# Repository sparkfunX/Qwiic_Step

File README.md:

SparkX Qwiic Step
========================================

[*SparkX Qwiic Step (SPX-15951)*](https://www.sparkfun.com/products/15951)

Qwiic Step features the A4988 stepper motor driver IC. Send commands using the I2C bus to configure your stepper motor movements. Easily attach and set up a limit switch or E-Stop and use our new favorite latching terminals to solderlessly and screwlessly attach motor and power.

Repository Contents
-------------------

* **/Documentation** - Data sheets, additional product information
* **/Firmware** - Firmware used on Qwiic Step
* **/Hardware** - Eagle design files (.brd, .sch)
* **/Production** - Production panel files (.brd)

Documentation
--------------
* **[SparkFun Qwiic Step Arduino Library](https://github.com/sparkfun/SparkFun_Qwiic_Step_Arduino_Library)** - Arduino library for the SparkX Qwiic Step.
* **[SparkFun Fritzing repo](https://github.com/sparkfun/Fritzing_Parts)** - Fritzing diagrams for SparkFun products.
* **[SparkFun 3D Model repo](https://github.com/sparkfun/3D_Models)** - 3D models of SparkFun products. 
* **[SparkFun Graphical Datasheets](https://github.com/sparkfun/Graphical_Datasheets)** -Graphical Datasheets for various SparkFun products.

License Information
-------------------

This product is _**open source**_! 

Please review the LICENSE.md file for license information. 

If you have any questions or concerns on licensing, please contact technical support on our [SparkFun forums](https://forum.sparkfun.com/viewforum.php?f=152).

Distributed as-is; no warranty is given.

- Your friends at SparkFun.

_<COLLABORATION CREDIT>_

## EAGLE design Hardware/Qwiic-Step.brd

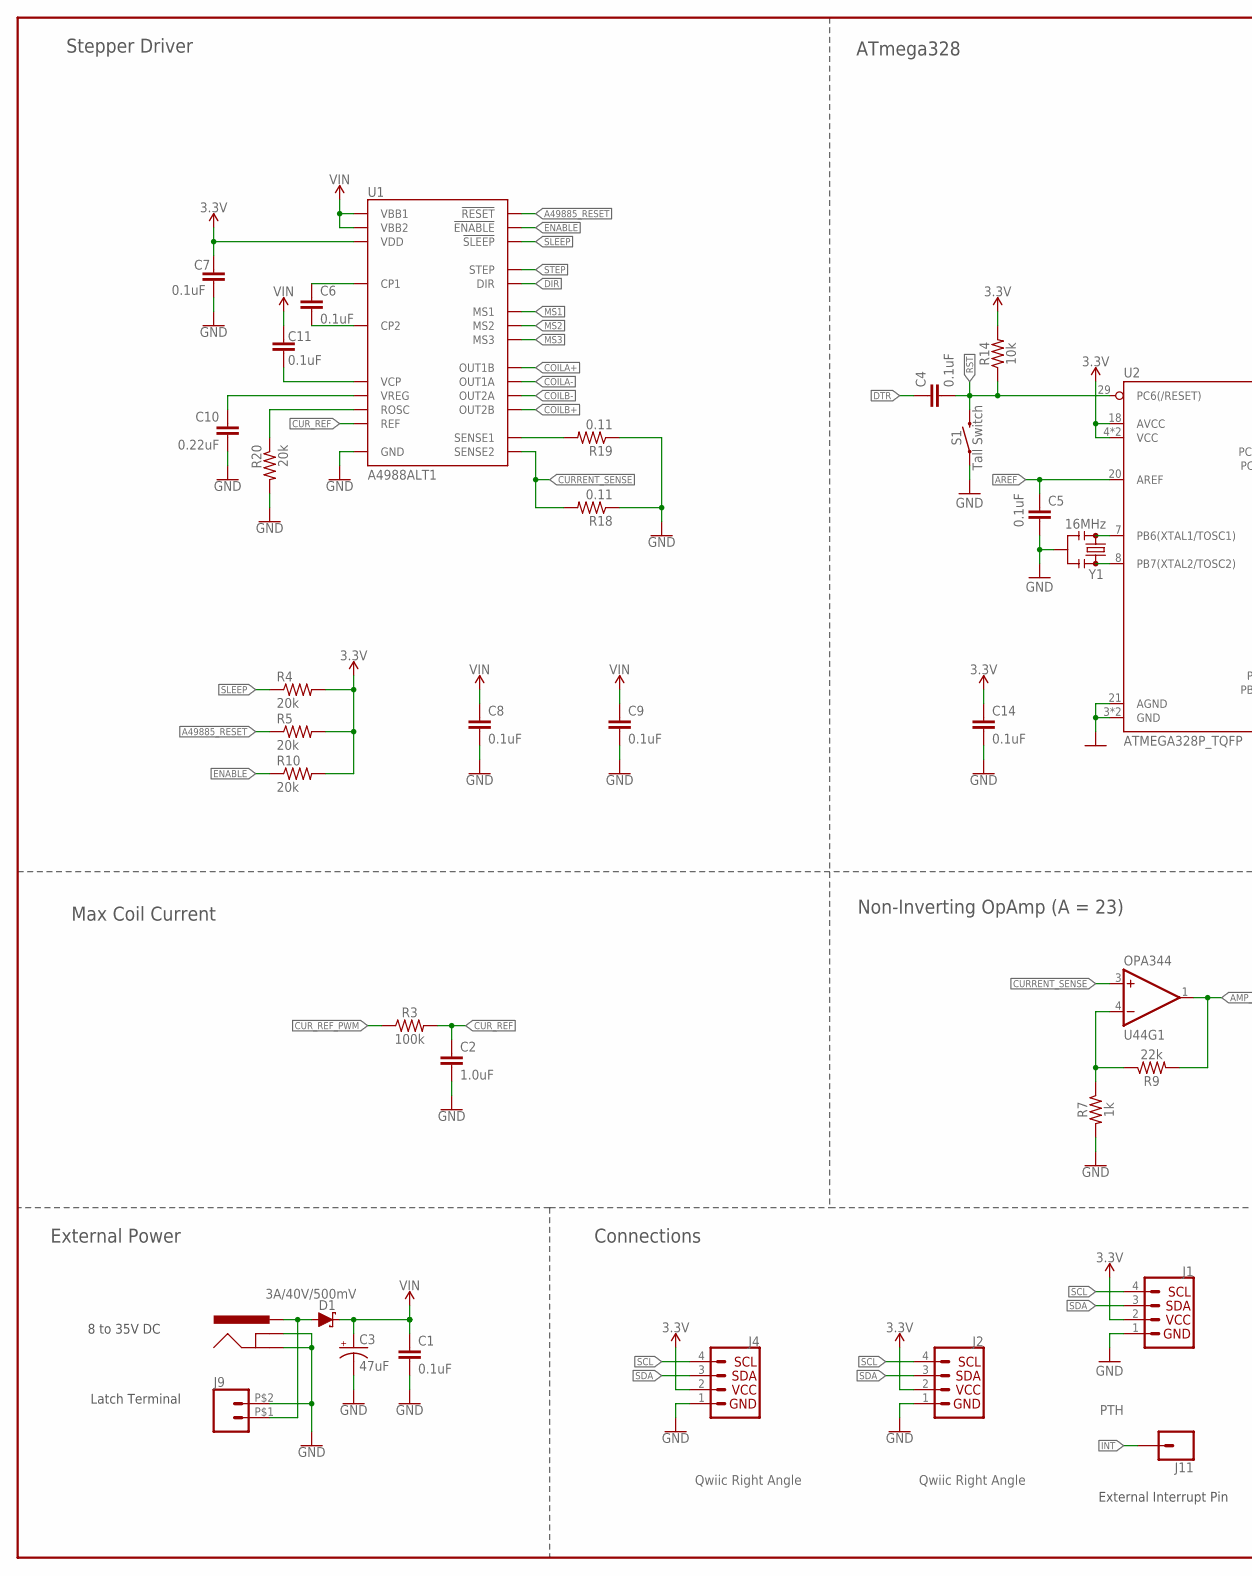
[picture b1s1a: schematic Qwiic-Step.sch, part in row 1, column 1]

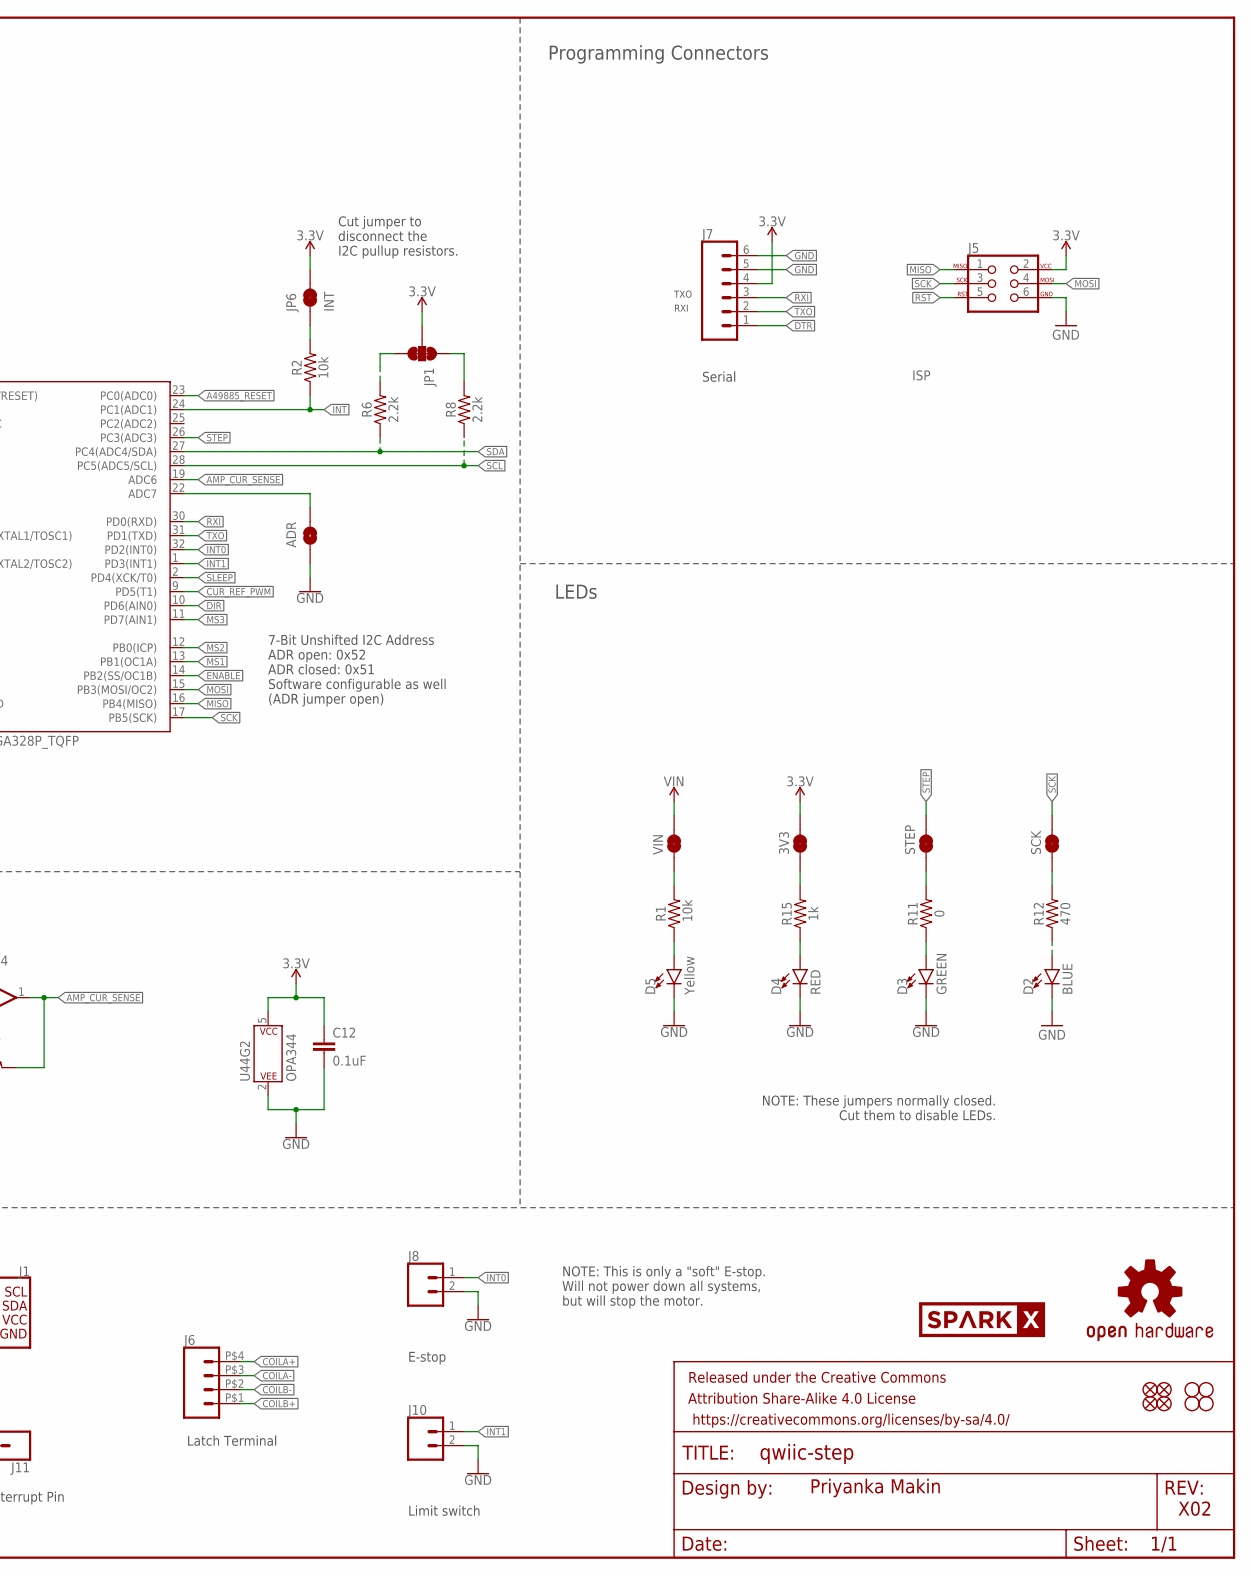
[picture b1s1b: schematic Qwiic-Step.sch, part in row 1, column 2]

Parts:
3V3: JUMPER-SMT_2_NC_TRACE_SILK; SMT-JUMPER_2_NC_TRACE_SILK
ADR: ADR; SMT-JUMPER_2_NO_SILK
C1, C4, C5, C6, C7, C8, C9, C11, C12, C14: 0.1uF; 0603
C2: 1.0uF; 0603
C3: 47uF; PANASONIC_D
C10: 0.22uF; 0603
D1: 3A/40V/500mV; SMA-DIODE
D2: BLUE; LED-0603
D3: GREEN; LED-0603
D4: RED; LED-0603
D5: Yellow; LED-0603
FD1, FD2, FD3, FD4: FIDUCIAL1X2; FIDUCIAL-1X2
FRAME2: FRAME-LEDGER; CREATIVE_COMMONS
J1: PTH; 1X04_NO_SILK
J2, J4: Qwiic Right Angle; JST04_1MM_RA
J3: 5.5x2.1mm Barrel; POWER_JACK_SMD
J5: ISP; 2X3_TEST_POINTS
J6: CONN_04LATCH; LATCHTERMINAL-5MM-4
J7: CONN_06NO_SILK_NO_POP; 1X06_NO_SILK
J8, J10: CONN_02-JST-2MM-SMT; JST-2-SMD
J9: CONN_02LATCH_2; LATCHTERMINAL-5MM-2
J11: CONN_01PTH_NO_SILK_YES_STOP; 1X01_NO_SILK
JP1: JUMPER-SMT_3_2-NC_TRACE_SILK; SMT-JUMPER_3_2-NC_TRACE_SILK
JP6: INT; SMT-JUMPER_2_NC_TRACE_SILK
JP7, JP8, JP9, JP10: STAND-OFF
LOGO1: OSHW-LOGOMINI; OSHW-LOGO-MINI
R1, R2, R14: 10k; 0603
R3: 100k; 0603
R4, R5, R10, R20: 20k; 0603
R6, R8: 2.2k; 0603
R7, R15: 1k; 0603
R9: 22k; 0603
R11: 0; 0603
R12: 470; 0603
R18, R19: 0.11; 2010
S1: Tall Switch; TACTILE_SWITCH_SMD_5.2MM
SCK: JUMPER-SMT_2_NC_TRACE_SILK; SMT-JUMPER_2_NC_TRACE_SILK
STEP: JUMPER-SMT_2_NC_TRACE_SILK; SMT-JUMPER_2_NC_TRACE_SILK
U1: A4988ALT1; QFN-28-5MM
U2: ATMEGA328P_TQFP; TQFP32-08
U44: OPA344; SOT23-5
U$49: SPARKX-LOGO4; SPARKX-MEDIUM
VIN: JUMPER-SMT_2_NC_TRACE_SILK; SMT-JUMPER_2_NC_TRACE_SILK
Y1: 16MHz; RESONATOR-SMD-3.2X1.3

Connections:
3.3V: 3V3.2, C7.1, C12.1, C14.1, J1.2 (VCC), J2.2, J4.2, J5.2, J7.4, JP1.2, JP6.2, R4.2, R5.2, R10.2, R14.2, U1.15 (VDD), U2.4 (VCC), U2.6 (VCC), U2.18 (AVCC), U44.5 (P$V+)
!ENABLE!: R10.1, U1.2 (!ENABLE!), U2.14 (PB2(SS/OC1B))
!RST!: C4.2, J5.5, R14.1, S1.3 (2), S1.4 (2), U2.29 (PC6(/RESET))
!SLEEP!: R4.1, U1.14 (!SLEEP!), U2.2 (PD4(XCK/T0))
A49885_!RESET!: R5.1, U1.12 (!RESET!), U2.23 (PC0(ADC0))
AMP_CUR_SENSE: R9.2, U2.19 (ADC6), U44.1 (OUT)
AREF: C5.1, U2.20 (AREF)
COILA+: J6.P$4 (4), U1.21 (OUT1B)
COILA-: J6.P$3 (3), U1.24 (OUT1A)
COILB+: J6.P$1 (1), U1.1 (OUT2B)
COILB-: J6.P$2 (2), U1.26 (OUT2A)
CURRENT_SENSE: R18.2, U1.27 (SENSE2), U44.3 (+IN)
CUR_REF: C2.1, R3.2, U1.17 (REF)
CUR_REF_PWM: R3.1, U2.9 (PD5(T1))
DIR: U1.19 (DIR), U2.10 (PD6(AIN0))
DTR: C4.1, J7.1
GND: ADR.2, C1.2, C2.2, C3.-, C5.2, C7.2, C8.2, C9.2, C10.2, C12.2, C14.2, D2.C, D3.C, D4.C, D5.C, J1.1 (GND), J2.1, J3.GND (GNDBREAK), J3.P$4 (GND), J4.1, J5.6, J7.5, J7.6, J8.2 (1), J9.P$2 (2), J10.2 (1), R7.2, R18.1, R19.1, R20.2, S1.1, S1.2 (1), U1.3 (GND), U1.18 (GND), U1.29 (GND), U2.3 (GND), U2.5 (GND), U2.21 (AGND), U44.2 (P$V-), Y1.2
INT: J11.1, R2.1, U2.24 (PC1(ADC1))
INT0: J8.1 (2), U2.32 (PD2(INT0))
INT1: J10.1 (2), U2.1 (PD3(INT1))
MISO: J5.1, U2.16 (PB4(MISO))
MOSI: J5.4, U2.15 (PB3(MOSI/OC2))
MS1: U1.9 (MS1), U2.13 (PB1(OC1A))
MS2: U1.10 (MS2), U2.12 (PB0(ICP))
MS3: U1.11 (MS3), U2.11 (PD7(AIN1))
unnamed: D3.A, R11.1
unnamed: R7.1, R9.1, U44.4 (-IN)
unnamed: R19.2, U1.23 (SENSE1)
unnamed: R1.2, VIN.1
unnamed: JP6.1, R2.2
unnamed: ADR.1, U2.22 (ADC7)
unnamed: D1.A, J3.VIN0 (PWR), J9.P$1 (1)
unnamed: C6.1, U1.4 (CP1)
unnamed: C6.2, U1.5 (CP2)
unnamed: D5.A, R1.1
unnamed: R11.2, STEP.1
unnamed: D2.A, R12.1
unnamed: U2.7 (PB6(XTAL1/TOSC1)), Y1.1
unnamed: U2.8 (PB7(XTAL2/TOSC2)), Y1.3
unnamed: JP1.3, R6.2
unnamed: JP1.1, R8.2
unnamed: R12.2, SCK.1
unnamed: R20.1, U1.13 (ROSC)
unnamed: C10.1, U1.8 (VREG)
unnamed: C11.1, U1.6 (VCP)
unnamed: D4.A, R15.1
unnamed: 3V3.1, R15.2
RXI: J7.3, U2.30 (PD0(RXD))
SCK: J5.3, SCK.2, U2.17 (PB5(SCK))
SCL: J1.4 (SCL), J2.4, J4.4, R8.1, U2.28 (PC5(ADC5/SCL))
SDA: J1.3 (SDA), J2.3, J4.3, R6.1, U2.27 (PC4(ADC4/SDA))
STEP: STEP.2, U1.16 (STEP), U2.26 (PC3(ADC3))
TXO: J7.2, U2.31 (PD1(TXD))
VIN: C1.1, C3.+, C8.1, C9.1, C11.2, D1.C, U1.22 (VBB1), U1.28 (VBB2), VIN.2

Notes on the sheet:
8 to 35V DC
Stepper Driver
Connections
Max Coil Current
External Power
ATmega328
TXO
RXI
Limit switch
E-stop
External Interrupt Pin
Latch Terminal
Priyanka Makin
X02
LEDs
Programming Connectors
Non-Inverting OpAmp (A = 23)
Serial
NOTE: These jumpers normally closed. Cut them to disable LEDs.
NOTE: This is only a "soft" E-stop. Will not power down all systems, but will stop the motor.
7-Bit Unshifted I2C Address ADR open: 0x52 ADR closed: 0x51 Software configurable as well (ADR jumper open)
Cut jumper to disconnect the I2C pullup resistors.

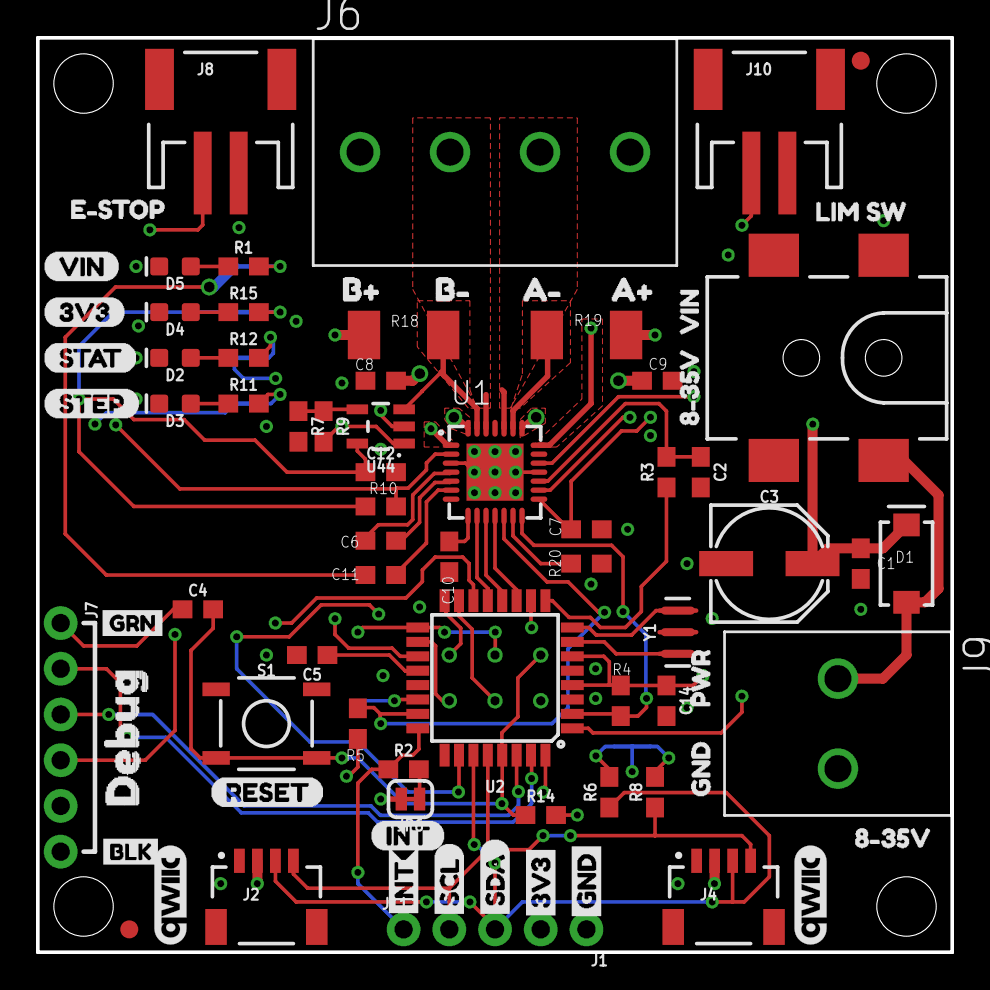
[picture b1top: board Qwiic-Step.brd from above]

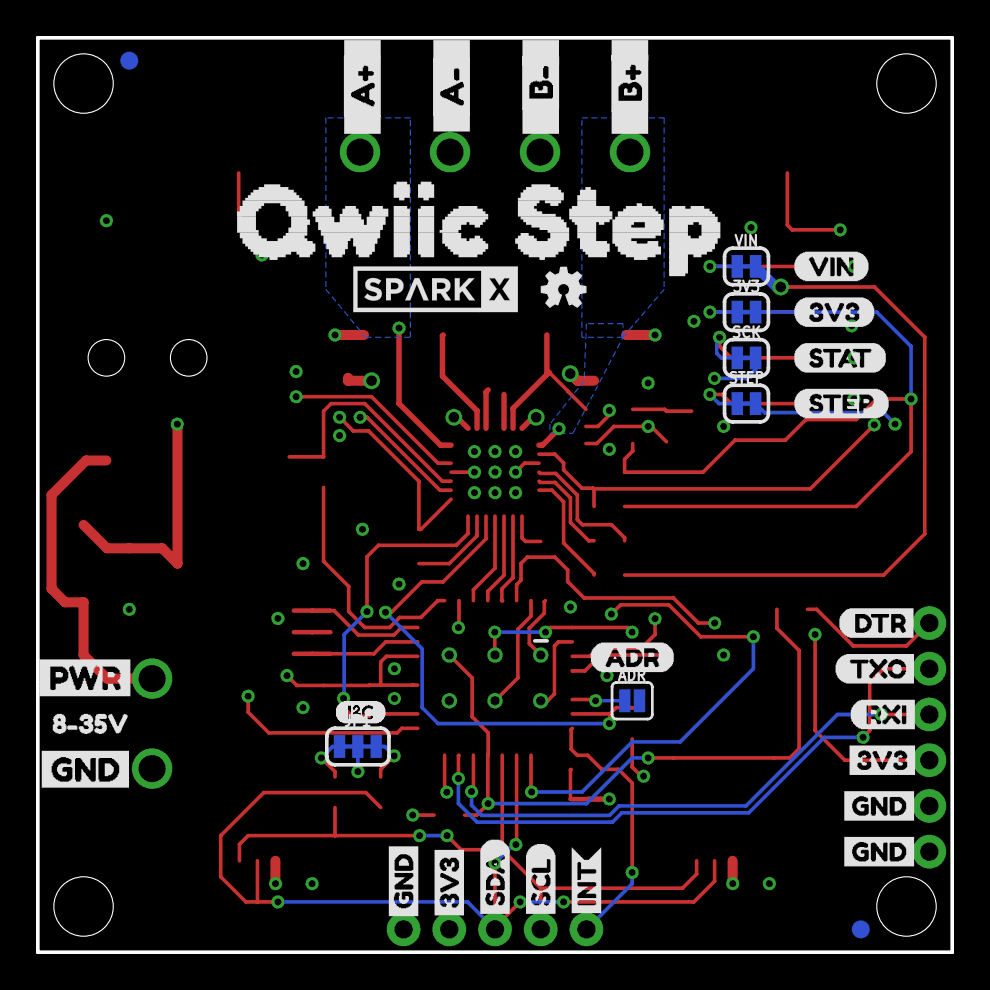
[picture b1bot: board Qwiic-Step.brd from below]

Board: 4 copper layers, 50.8 x 50.8 mm, 122 parts (37 on the bottom side), 54 nets.

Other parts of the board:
U$1: 3V30
U$2: 3V37
U$3: GND8
U$4: STAT5
U$5: SCL5
U$6: SDA6
U$7: STEP4
U$8: VIN3
U$9, U$29: QWIIC_5.5MM
U$10, U$11, U$40: 8#35V0
U$12: VIN1
U$13: STAT0
U$14: E#STOP2
U$15, U$16: I_SUPER2_C-()-03
U$17, U$45: 3V31
U$18: DTR4
U$19: DEBUG0
U$20: BLK2
U$21, U$22, U$44: GND0
U$23: LIM_SW3
U$24, U$30: INT4
U$25: ADR0
U$26: 3V35
U$27: RESET1
U$28: GRN1
U$31: GND6
U$32, U$54: A#2
U$33: SDA4
U$34: SCL3
U$35: RXI3
U$36, U$55: A#3
U$37: STEP2
U$38: VIN0
U$41: INT2
U$42: GND1
U$43: PWR0
U$46, U$57: B#4
U$47, U$58: B#5
U$48: TXO2
U$53: PWR1
U$56: QWIIC_STEP0

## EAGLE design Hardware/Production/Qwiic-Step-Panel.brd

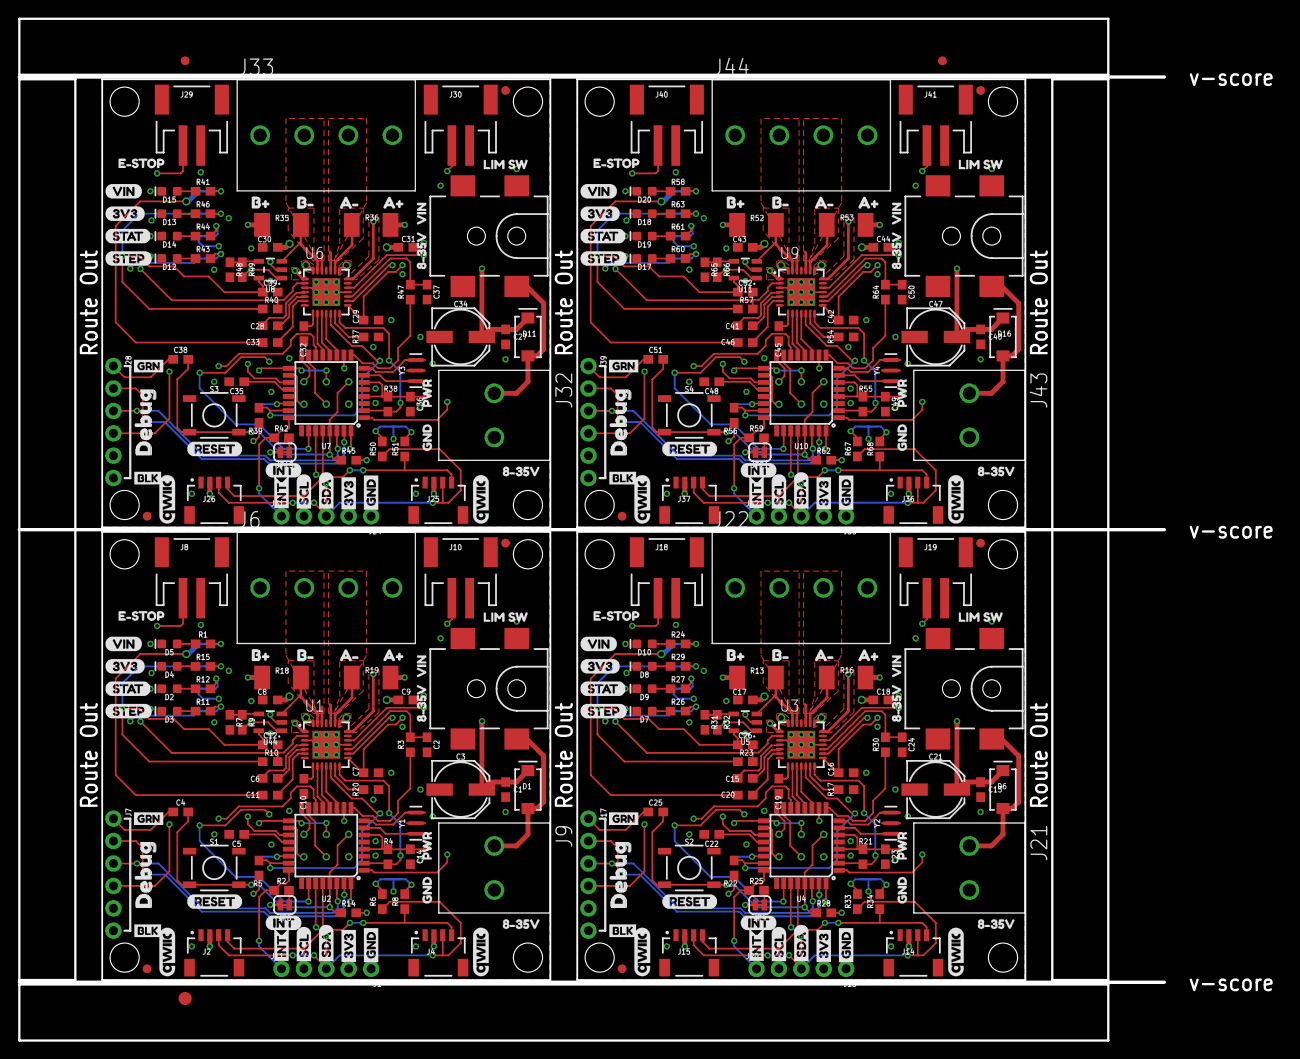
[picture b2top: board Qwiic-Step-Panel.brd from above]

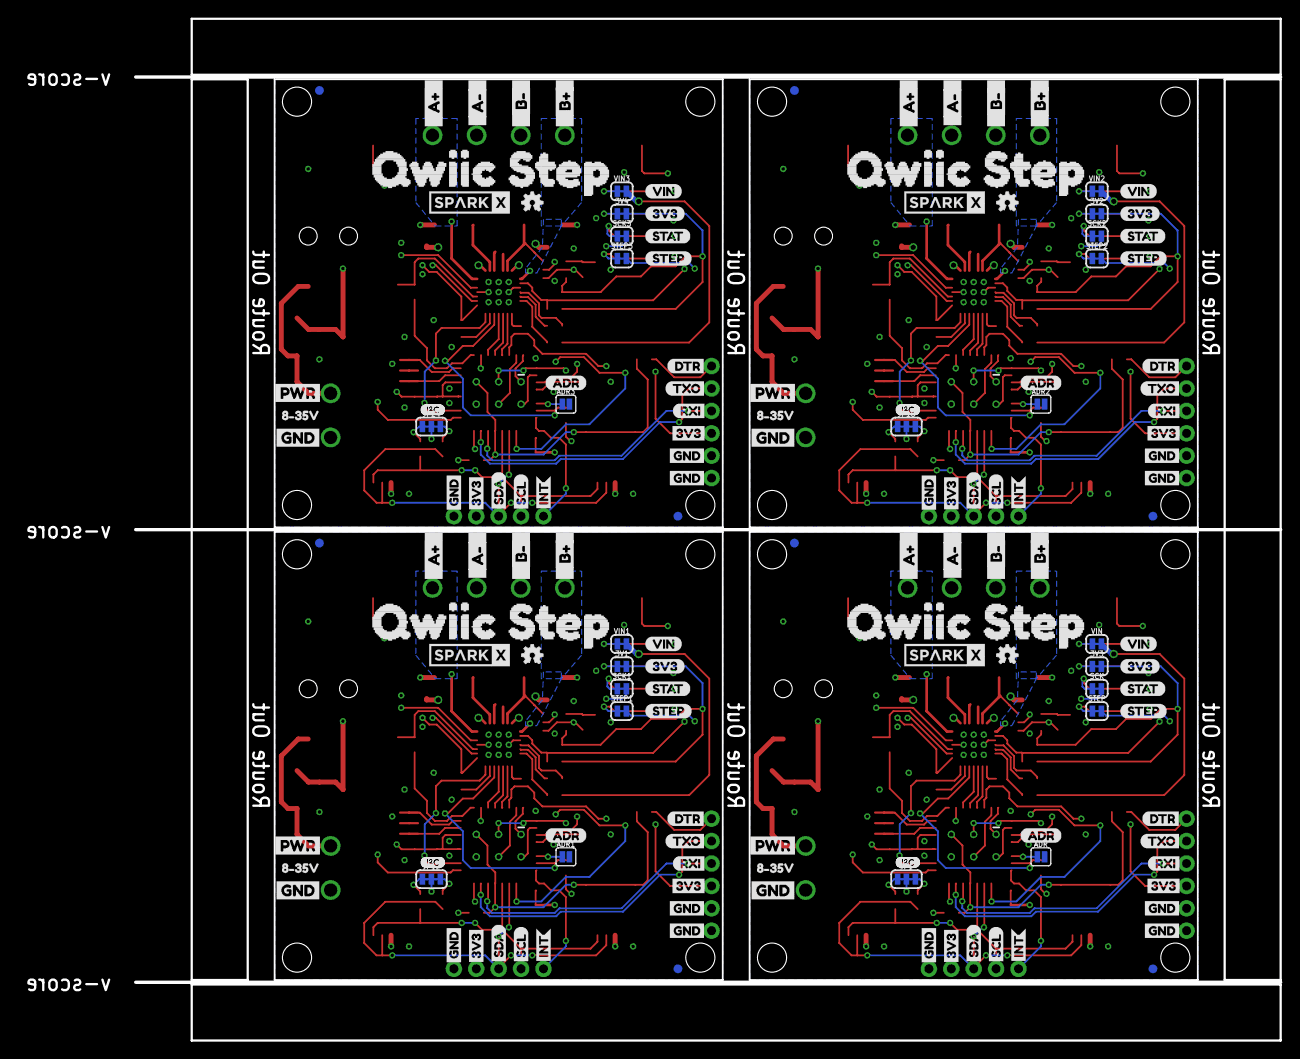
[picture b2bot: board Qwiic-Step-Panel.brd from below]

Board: 4 copper layers, 143.0 x 115.7 mm, 487 parts (148 on the bottom side), 216 nets.

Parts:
3V1, 3V2, 3V3, 3V4: JUMPER-SMT_2_NC_TRACE_SILK; SMT-JUMPER_2_NC_TRACE_SILK
ADR, ADR1, ADR2, ADR3: ADR; SMT-JUMPER_2_NO_SILK
C1, C4, C5, C6, C7, C8, C9, C11, C12, C13, C14, C15, C16, C17, C18, C20, C22, C23, C25, C26, C27, C28, C29, C30, C31, C33, C35, C36, C38, C39, C40, C41, C42, C43, C44, C46, C48, C49, C51, C52: 0.1uF; 0603
C2, C24, C37, C50: 10nF; 0603
C3, C21, C34, C47: 47uF; PANASONIC_D
C10, C19, C32, C45: 0.22uF; 0603
D1, D6, D11, D16: 3A/40V/500mV; SMA-DIODE
D2, D9, D14, D19: BLUE; LED-0603
D3, D7, D12, D17: GREEN; LED-0603
D4, D8, D13, D18: RED; LED-0603
D5, D10, D15, D20: Yellow; LED-0603
E$1, E$2: FIDUCIAL-1X2
E$3: FIDUCIAL-1.5X3
FD1, FD2, FD3, FD4, FD5, FD6, FD7, FD8, FD9, FD10, FD11, FD12, FD13, FD14, FD15, FD16: FIDUCIAL1X2; FIDUCIAL-1X2
J1, J13, J24, J35: PTH; 1X04_NO_SILK
J2, J4, J14, J15, J25, J26, J36, J37: Qwiic Right Angle; JST04_1MM_RA
J3, J12, J23, J34: 5.5x2.1mm Barrel; POWER_JACK_SMD
J5, J16, J27, J38: ISP; 2X3_TEST_POINTS
J6, J22, J33, J44: LATCHTERMINAL-5MM-4
J7, J17, J28, J39: 1X06_NO_SILK
J8, J10, J18, J19, J29, J30, J40, J41: JST-2-SMD
J9, J21, J32, J43: LATCHTERMINAL-5MM-2
J11, J20, J31, J42: 1X01_NO_SILK
JP1, JP12, JP18, JP24: SMT-JUMPER_3_2-NC_TRACE_SILK
JP2, JP3, JP5, JP7, JP8, JP9, JP10, JP11, JP13, JP14, JP16, JP17, JP19, JP20, JP22, JP23: STAND-OFF
JP4, JP6, JP15, JP21: INT; SMT-JUMPER_2_NC_TRACE_SILK
LOGO1, LOGO2, LOGO3, LOGO4: OSHW-LOGOMINI; OSHW-LOGO-MINI
R1, R24, R41, R58: 4.7k; 0603
R2, R14, R25, R28, R42, R45, R59, R62: 10k; 0603
R3, R30, R47, R64: 33k; 0603
R4, R5, R10, R17, R20, R21, R22, R23, R37, R38, R39, R40, R54, R55, R56, R57: 20k; 0603
R6, R8, R33, R34, R50, R51, R67, R68: 2.2k; 0603
R7, R11, R15, R26, R29, R31, R43, R46, R48, R60, R63, R65: 1k; 0603
R9, R32, R49, R66: 22k; 0603
R12, R27, R44, R61: 470; 0603
R13, R16, R18, R19, R35, R36, R52, R53: 0.11; 2010
S1, S2, S3, S4: Tall Switch; TACTILE_SWITCH_SMD_5.2MM
SCK, SCK1, SCK2, SCK3: JUMPER-SMT_2_NC_TRACE_SILK; SMT-JUMPER_2_NC_TRACE_SILK
STEP, STEP1, STEP2, STEP3: JUMPER-SMT_2_NC_TRACE_SILK; SMT-JUMPER_2_NC_TRACE_SILK
U1, U3, U6, U9: A4988ALT1; QFN-28-5MM
U2, U4, U7, U10: ATMEGA328P_TQFP; TQFP32-08
U5, U8, U11, U44: OPA344; SOT23-5
U$1, U$39, U$109, U$163: 3V30
U$2, U$50, U$110, U$164: 3V37
U$3, U$51, U$111, U$165: GND8
U$4, U$62, U$116, U$170: STAT5
U$5, U$52, U$112, U$166: SCL5
U$6, U$59, U$113, U$167: SDA6
U$7, U$60, U$114, U$168: STEP4
U$8, U$61, U$115, U$169: VIN3
U$9, U$29, U$65, U$74, U$119, U$128, U$173, U$182: QWIIC_5.5MM
U$10, U$11, U$40, U$66, U$67, U$99, U$120, U$121, U$153, U$174, U$175, U$207: 8#35V0
U$12, U$68, U$122, U$176: VIN1
U$13, U$106, U$160, U$214: STAT0
U$14, U$69, U$123, U$177: E#STOP2
U$15, U$16, U$107, U$108, U$161, U$162, U$215, U$216: I_SUPER2_C-()-03
U$17, U$45, U$83, U$91, U$137, U$145, U$191, U$199: 3V31
U$18, U$92, U$146, U$200: DTR4
U$19, U$98, U$152, U$206: DEBUG0
U$20, U$63, U$117, U$171: BLK2
U$21, U$22, U$44, U$93, U$94, U$100, U$147, U$148, U$154, U$201, U$202, U$208: GND0
U$23, U$70, U$124, U$178: LIM_SW3
U$24, U$30, U$71, U$75, U$125, U$129, U$179, U$183: INT4
U$25, U$72, U$126, U$180: ADR0
U$26, U$76, U$130, U$184: 3V35
U$27, U$73, U$127, U$181: RESET1
U$28, U$64, U$118, U$172: GRN1
U$31, U$77, U$131, U$185: GND6
U$32, U$54, U$87, U$102, U$141, U$156, U$195, U$210: A#2
U$33, U$78, U$132, U$186: SDA4
U$34, U$79, U$133, U$187: SCL3
U$35, U$95, U$149, U$203: RXI3
U$36, U$55, U$88, U$103, U$142, U$157, U$196, U$211: A#3
U$37, U$84, U$138, U$192: STEP2
U$38, U$85, U$139, U$193: VIN0
U$41, U$80, U$134, U$188: INT2
U$42, U$81, U$135, U$189: GND1
U$43, U$82, U$136, U$190: PWR0
U$46, U$57, U$89, U$104, U$143, U$158, U$197, U$212: B#4
U$47, U$58, U$90, U$105, U$144, U$159, U$198, U$213: B#5
U$48, U$96, U$150, U$204: TXO2
U$49, U$97, U$151, U$205: SPARKX-LOGO4; SPARKX-MEDIUM
U$53, U$101, U$155, U$209: PWR1
U$56, U$86, U$140, U$194: QWIIC_STEP0
VIN, VIN1, VIN2, VIN3: JUMPER-SMT_2_NC_TRACE_SILK; SMT-JUMPER_2_NC_TRACE_SILK
Y1, Y2, Y3, Y4: 16MHz; RESONATOR-SMD-3.2X1.3

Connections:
3.3V: 3V3.2, C7.1, C12.1, C14.1, J1.2, J2.2, J4.2, J5.2, J7.4, JP1.2, JP6.2, R4.2, R5.2, R10.2, R14.2, U1.15, U2.4, U2.6, U2.18, U44.5
3.3V1: 3V1.2, C16.1, C23.1, C26.1, J13.2, J14.2, J15.2, J16.2, J17.4, JP4.2, JP12.2, R21.2, R22.2, R23.2, R28.2, U3.15, U4.4, U4.6, U4.18, U5.5
3.3V2: 3V2.2, C29.1, C36.1, C39.1, J24.2, J25.2, J26.2, J27.2, J28.4, JP15.2, JP18.2, R38.2, R39.2, R40.2, R45.2, U6.15, U7.4, U7.6, U7.18, U8.5
3.3V3: 3V4.2, C42.1, C49.1, C52.1, J35.2, J36.2, J37.2, J38.2, J39.4, JP21.2, JP24.2, R55.2, R56.2, R57.2, R62.2, U9.15, U10.4, U10.6, U10.18, U11.5
!ENABLE!: R10.1, U1.2, U2.14
!ENABLE!1: R23.1, U3.2, U4.14
!ENABLE!2: R40.1, U6.2, U7.14
!ENABLE!3: R57.1, U9.2, U10.14
!RST!: C4.2, J5.5, R14.1, S1.3, S1.4, U2.29
!RST!1: C25.2, J16.5, R28.1, S2.3, S2.4, U4.29
!RST!2: C38.2, J27.5, R45.1, S3.3, S3.4, U7.29
!RST!3: C51.2, J38.5, R62.1, S4.3, S4.4, U10.29
!SLEEP!: R4.1, U1.14, U2.2
!SLEEP!1: R21.1, U3.14, U4.2
!SLEEP!2: R38.1, U6.14, U7.2
!SLEEP!3: R55.1, U9.14, U10.2
A49885_!RESET!: R5.1, U1.12, U2.23
A49885_!RESET!1: R22.1, U3.12, U4.23
A49885_!RESET!2: R39.1, U6.12, U7.23
A49885_!RESET!3: R56.1, U9.12, U10.23
AMP_CUR_SENSE: R9.2, U2.19, U44.1
AMP_CUR_SENSE1: R32.2, U4.19, U5.1
AMP_CUR_SENSE2: R49.2, U7.19, U8.1
AMP_CUR_SENSE3: R66.2, U10.19, U11.1
AREF: C5.1, U2.20
AREF1: C22.1, U4.20
AREF2: C35.1, U7.20
AREF3: C48.1, U10.20
COILA+: J6.P$4, U1.21
COILA+1: J22.P$4, U3.21
COILA+2: J33.P$4, U6.21
COILA+3: J44.P$4, U9.21
COILA-: J6.P$3, U1.24
COILA-1: J22.P$3, U3.24
COILA-2: J33.P$3, U6.24
COILA-3: J44.P$3, U9.24
COILB+: J6.P$1, U1.1
COILB+1: J22.P$1, U3.1
COILB+2: J33.P$1, U6.1
COILB+3: J44.P$1, U9.1
COILB-: J6.P$2, U1.26
COILB-1: J22.P$2, U3.26
COILB-2: J33.P$2, U6.26
COILB-3: J44.P$2, U9.26
CURRENT_SENSE: R18.2, U1.27, U44.3
CURRENT_SENSE1: R13.2, U3.27, U5.3
CURRENT_SENSE2: R35.2, U6.27, U8.3
CURRENT_SENSE3: R52.2, U9.27, U11.3
CUR_REF: C2.1, R3.2, U1.17
CUR_REF1: C24.1, R30.2, U3.17
CUR_REF2: C37.1, R47.2, U6.17
CUR_REF3: C50.1, R64.2, U9.17
CUR_REF_PWM: R3.1, U2.9
CUR_REF_PWM1: R30.1, U4.9
CUR_REF_PWM2: R47.1, U7.9
CUR_REF_PWM3: R64.1, U10.9
DIR: U1.19, U2.10
DIR1: U3.19, U4.10
DIR2: U6.19, U7.10
DIR3: U9.19, U10.10
DTR: C4.1, J7.1
DTR1: C25.1, J17.1
DTR2: C38.1, J28.1
DTR3: C51.1, J39.1
GND: ADR.2, C1.2, C2.2, C3.-, C5.2, C7.2, C8.2, C9.2, C10.2, C12.2, C14.2, D2.C, D3.C, D4.C, D5.C, J1.1, J2.1, J3.GND, J3.P$4, J4.1, J5.6, J7.5, J7.6, J8.2, J9.P$2, J10.2, R7.2, R18.1, R19.1, R20.2, S1.1, S1.2, U1.3, U1.18, U1.29, U2.3, U2.5, U2.21, U44.2, Y1.2
GND1: ADR1.2, C13.2, C16.2, C17.2, C18.2, C19.2, C21.-, C22.2, C23.2, C24.2, C26.2, D7.C, D8.C, D9.C, D10.C, J12.GND, J12.P$4, J13.1, J14.1, J15.1, J16.6, J17.5, J17.6, J18.2, J19.2, J21.P$2, R13.1, R16.1, R17.2, R31.2, S2.1, S2.2, U3.3, U3.18, U3.29, U4.3, U4.5, U4.21, U5.2, Y2.2
GND2: ADR2.2, C27.2, C29.2, C30.2, C31.2, C32.2, C34.-, C35.2, C36.2, C37.2, C39.2, D12.C, D13.C, D14.C, D15.C, J23.GND, J23.P$4, J24.1, J25.1, J26.1, J27.6, J28.5, J28.6, J29.2, J30.2, J32.P$2, R35.1, R36.1, R37.2, R48.2, S3.1, S3.2, U6.3, U6.18, U6.29, U7.3, U7.5, U7.21, U8.2, Y3.2
GND3: ADR3.2, C40.2, C42.2, C43.2, C44.2, C45.2, C47.-, C48.2, C49.2, C50.2, C52.2, D17.C, D18.C, D19.C, D20.C, J34.GND, J34.P$4, J35.1, J36.1, J37.1, J38.6, J39.5, J39.6, J40.2, J41.2, J43.P$2, R52.1, R53.1, R54.2, R65.2, S4.1, S4.2, U9.3, U9.18, U9.29, U10.3, U10.5, U10.21, U11.2, Y4.2
INT: J11.1, R2.1, U2.24
INT0: J8.1, U2.32
INT1: J10.1, U2.1
INT2: J20.1, R25.1, U4.24
INT3: J18.1, U4.32
INT4: J19.1, U4.1
INT5: J31.1, R42.1, U7.24
INT6: J29.1, U7.32
INT7: J30.1, U7.1
INT8: J42.1, R59.1, U10.24
INT9: J40.1, U10.32
INT10: J41.1, U10.1
MISO: J5.1, U2.16
MISO1: J16.1, U4.16
MISO2: J27.1, U7.16
MISO3: J38.1, U10.16
MOSI: J5.4, U2.15
MOSI1: J16.4, U4.15
MOSI2: J27.4, U7.15
MOSI3: J38.4, U10.15
MS1: U1.9, U2.13
MS2: U1.10, U2.12
MS3: U1.11, U2.11
MS4: U3.10, U4.12
MS5: U3.11, U4.11
MS6: U3.9, U4.13
MS7: U6.10, U7.12
MS8: U6.11, U7.11
MS9: U6.9, U7.13
MS10: U9.10, U10.12
MS11: U9.11, U10.11
MS12: U9.9, U10.13
unnamed: D3.A, R11.1
unnamed: R7.1, R9.1, U44.4
unnamed: R19.2, U1.23
unnamed: R1.2, VIN.1
unnamed: JP6.1, R2.2
unnamed: ADR.1, U2.22
unnamed: D1.A, J3.VIN0, J9.P$1
unnamed: C6.1, U1.4
unnamed: C6.2, U1.5
unnamed: D5.A, R1.1
unnamed: R11.2, STEP.1
unnamed: D2.A, R12.1
unnamed: U2.7, Y1.1
unnamed: U2.8, Y1.3
unnamed: JP1.3, R6.2
unnamed: JP1.1, R8.2
unnamed: R12.2, SCK.1
unnamed: C15.1, U3.4
unnamed: R20.1, U1.13
unnamed: C10.1, U1.8
unnamed: C11.1, U1.6
unnamed: C15.2, U3.5
unnamed: R17.1, U3.13
unnamed: C19.1, U3.8
unnamed: C20.1, U3.6
unnamed: D4.A, R15.1
unnamed: 3V3.1, R15.2
unnamed: D10.A, R24.1
unnamed: R24.2, VIN1.1
unnamed: D6.A, J12.VIN0, J21.P$1
unnamed: D7.A, R26.1
unnamed: R26.2, STEP1.1
unnamed: U4.7, Y2.1
unnamed: U4.8, Y2.3
unnamed: D8.A, R29.1
unnamed: 3V1.1, R29.2
unnamed: JP4.1, R25.2
unnamed: R31.1, R32.1, U5.4
unnamed: R16.2, U3.23
unnamed: ADR1.1, U4.22
unnamed: D9.A, R27.1
unnamed: JP12.3, R33.2
unnamed: JP12.1, R34.2
unnamed: R27.2, SCK1.1
unnamed: C28.1, U6.4
unnamed: C28.2, U6.5
unnamed: R37.1, U6.13
unnamed: C32.1, U6.8
unnamed: C33.1, U6.6
unnamed: D15.A, R41.1
unnamed: R41.2, VIN2.1
unnamed: D11.A, J23.VIN0, J32.P$1
unnamed: D12.A, R43.1
unnamed: R43.2, STEP2.1
unnamed: U7.7, Y3.1
unnamed: U7.8, Y3.3
unnamed: D13.A, R46.1
unnamed: 3V2.1, R46.2
unnamed: JP15.1, R42.2
unnamed: R48.1, R49.1, U8.4
unnamed: R36.2, U6.23
unnamed: ADR2.1, U7.22
unnamed: D14.A, R44.1
unnamed: JP18.3, R50.2
unnamed: JP18.1, R51.2
unnamed: R44.2, SCK2.1
unnamed: C41.1, U9.4
unnamed: C41.2, U9.5
unnamed: R54.1, U9.13
unnamed: C45.1, U9.8
unnamed: C46.1, U9.6
unnamed: D20.A, R58.1
unnamed: R58.2, VIN3.1
unnamed: D16.A, J34.VIN0, J43.P$1
unnamed: D17.A, R60.1
unnamed: R60.2, STEP3.1
unnamed: U10.7, Y4.1
unnamed: U10.8, Y4.3
unnamed: D18.A, R63.1
unnamed: 3V4.1, R63.2
unnamed: JP21.1, R59.2
unnamed: R65.1, R66.1, U11.4
unnamed: R53.2, U9.23
unnamed: ADR3.1, U10.22
unnamed: D19.A, R61.1
unnamed: JP24.3, R67.2
unnamed: JP24.1, R68.2
unnamed: R61.2, SCK3.1
RXI: J7.3, U2.30
RXI1: J17.3, U4.30
RXI2: J28.3, U7.30
RXI3: J39.3, U10.30
SCK: J5.3, SCK.2, U2.17
SCK1: J16.3, SCK1.2, U4.17
SCK2: J27.3, SCK2.2, U7.17
SCK3: J38.3, SCK3.2, U10.17
SCL: J1.4, J2.4, J4.4, R8.1, U2.28
SCL1: J13.4, J14.4, J15.4, R34.1, U4.28
SCL2: J24.4, J25.4, J26.4, R51.1, U7.28
SCL3: J35.4, J36.4, J37.4, R68.1, U10.28
SDA: J1.3, J2.3, J4.3, R6.1, U2.27
SDA1: J13.3, J14.3, J15.3, R33.1, U4.27
SDA2: J24.3, J25.3, J26.3, R50.1, U7.27
SDA3: J35.3, J36.3, J37.3, R67.1, U10.27
STEP: STEP.2, U1.16, U2.26
STEP1: STEP1.2, U3.16, U4.26
STEP2: STEP2.2, U6.16, U7.26
STEP3: STEP3.2, U9.16, U10.26
TXO: J7.2, U2.31
TXO1: J17.2, U4.31
TXO2: J28.2, U7.31
TXO3: J39.2, U10.31
VIN: C1.1, C3.+, C8.1, C9.1, C11.2, D1.C, U1.22, U1.28, VIN.2
VIN1: C13.1, C17.1, C18.1, C20.2, C21.+, D6.C, U3.22, U3.28, VIN1.2
VIN2: C27.1, C30.1, C31.1, C33.2, C34.+, D11.C, U6.22, U6.28, VIN2.2
VIN3: C40.1, C43.1, C44.1, C46.2, C47.+, D16.C, U9.22, U9.28, VIN3.2

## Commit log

2019-11-12 temporary 4 layer
2019-11-12 Reduce to 2 layers
2019-11-12 Add git ignore. Remove # backups. Move hardware to sub dir.
2019-11-12 Add INT pin. Remap ISP connector.
2019-11-12 Add limit switches
2019-11-13 New board layout. Added current sense.
2019-11-19 Removed generated libraries and finishing up layout
2019-11-19 Changes to polygon classes
2019-11-20 Final board layout
2019-12-09 Initial firmware commit
2019-12-09 Trying to get motor to turn
2019-12-13 Wrote printState and convertToFloat functions
    Reading/writing to struct does not work as expected when you are dealing with a float (setSpeed, maxSpeed, acceleration)
2019-12-16 Working on updateStepper/accelstepper function
2019-12-17 UpdateStepper function and interrupt handling
2019-12-18 Working on EEPROM and nvm
2019-12-20 Superficial function name changes and board update
    Rev 2 of Qwiic Step board! Fixed: MOSI was not connected to ISP pins! Adjusted MOSI and ADR jumper
2020-01-07 got interrupt functionality working, but broke motor movement...
    Working on solidifying the correct logic for updateStepper() function. This is what actually controlls motor movement.
2020-01-08 Adjusting updateStepper function
2020-01-08 I'm not sure
2020-01-09 Move pin defs to hardware gates. Add comments. Remove unused var.
2020-01-09 Uppercase PIN constants.
2020-01-09 Adding dev platform protection gates. Removing old comments.
2020-01-09 Remove pullup from INT. Update commenrts.
2020-01-09 Remove pass by reference on startI2C
2020-01-09 Mvoe function to helper tab. Print status with floats.
2020-01-09 Add serial debug menu
2020-01-09 Add acceleration and isRunning checks to updateMotorStatus()
2020-01-09 Fix collision problems. Now compiles
2020-01-10 Updated limit switch interrupt functionality
2020-01-10 Adding/testing stop on limit switch press functionality
2020-01-10 Change guards from ATTiny to PRODUCTION_TARTGET gate
2020-01-10 Rename updateFlag to newData.
2020-01-10 Working through the limit switch ISR and the different motor run options.
    Things are not quite behaving as expected currently. The plan is to continue/finish implementing the different motor run options, make sure they function as intended. Then go back and fix the things 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
2020-01-10 Prelim interrupts working.
2020-01-13 Improving Move value testing
    We now check to see if user has written to the move register rather than doing the illegal value check. This enables the ability to do a getMove() to find out what value is stored there.
2020-01-13 Move value correctly check when written to. Added stop ability is user writes move(0).
2020-01-13 Adding isReached state machine. Rename INT state machine.
2020-01-13 Remove hasMoved var. Now covered by MOVE state machine. Add change timeout to accel/decel checking.
2020-01-13 isReached is working well. Accel/decel now exhibiting correctly.
2020-01-13 Working on run options and implemented distanceToGo in registerMap. Made an example to demonstrate how runSpeedToPosition is meant to work.
2020-01-14 isLimited and isReached interrupts working
2020-01-14 Add mode changes based on motorcontrol register.
2020-01-14 Adding debounce to limit switch interrupt
2020-01-14 Remove old test firmware. Add new tests.
2020-01-14 Fix bug in setSpeed function.
2020-01-14 First swing at updating currents
2020-01-14 Add hard stop command. Add setSpeed(0) to softStop command.
2020-01-14 Working runSpeedToPos. Move functions to helpers.
2020-01-14 Change bit position and rename modes.
2020-01-14 Implemented change current state machine and calculate pwm current function
2020-01-14 Add mode block to setSpeed.
2020-01-14 Remove delay in speed change.
    I believe the speed value was getting over written when we were in accel mode. Now that we have the guard, it seems to be behaving.
2020-01-15 semi-colon
2020-01-15 Updated Qwiic Step board, working on examples for Rev 1 hardware
    Updates to board:
    Fixed serial programming pins
    Moved ADR jumper to MOSI pin to free up GPIO
    Moved A49885 reset pin to GPIO (from analog input pin)
2020-01-15 Got PWM control and current sensing examples to work.
2020-01-17 Move update of parameters and registers into interrupt to allow for clock stretching. Add disable output support.
2020-01-17 Get setPosition command working.
2020-01-17 Add disableOutputs when we reach our position, option.
2020-01-17 Add disableMotorsOnEStop feature.
2020-01-18 Headless operation starting to work
2020-01-20 Adding checks for registers in updateParameters for NVM storage.
2020-01-20 Move hardcoded EEPROM locations to global defines.
2020-01-20 Enable pull up on int pin on dev board.
2020-01-20 Only calc accel/decel bits if in accel mode.
2020-01-20 Add state machine for I2C address jumper
2020-01-20 Correct accel/decel checks when motor is moving CCW.
2020-01-21 Restart I2C if address is changed. Add hardStop() function. Correctly set disableMotor bit in case of EStop or isReached settings satisfied.
2020-01-21 Add helper print functions to hold/run current registers.
2020-03-11 Update run with correct enable active low
2020-03-11 Add production pins to test sketch
2020-03-11 Rev X02 finally done?
2020-03-11 All traces routed, READY FOR BOARD REVIEW (other than some minor silk updates that I'll do tomorrow morning).
2020-03-11 Superficial silk changes. Cleaned up wire stubs
2020-03-11 Added amplifier circuit to current sense reading
2020-03-11 Final layout changes. Fixinging polygons, routing, and thermal relief
2020-03-11 Cleaning up Rev 1 changes. Still need to connect current sense trace, run DRC.
2020-03-11 Removed current sense IC. Switched around ADC pins
2020-03-11 Rev X02 finalized and ordered
2020-03-11 Add currentPWMControl and CurrentSense from hardwarechanges branch
2020-03-11 Pin name and value changes to get compatible with x02 hardware
2020-03-11 Workaround for lack of pullup on ADC7
    ADC6/7 have no internal pullups. ADC7 is checked as the ADR jumper at power up. Since pin is floating, we can do an ADC on the pin and see if it is zero (closed) or non-zero (floating / open). Not bu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
2020-03-11 Remove print gates
2020-03-11 Change resistor values on VIN and STEP LEDs.
2020-03-11 Change pin numbers on current sensing sketch to match x02.
2020-03-11 Current sensing mostly working.
2020-03-12 Adding test menu to current sense sketch to make taking measurements easier.
2020-03-12 Increasing yellow LED resistor to 10k to limit brightness
2020-03-12 Change CUR_REF_PWM RC filter to 100k/1uF.
2020-03-12 Rename test sketch
2020-03-19 Change PWM filter to use X7R rated cap.
2020-03-19 Covert hold/run current to voltage.
2020-03-19 Fixed type conversion on run/hold voltage floats.
2020-03-23 Generated binaries and wrote batch file
2020-03-23 Regenerated hex files
2020-03-23 Trying to upload firmware WITH bootloader
2020-03-24 Updated batch file and .hex
    Batch file now flashes bootloader and firmware correctly
2020-03-26 Generated files for product page
2020-08-04 Update program_qwiic_step.bat
    Add fuse bits
2021-08-28 Move EEPROM writes out of ISR to allow reception of multiple settings.
2021-08-28 Adding programming instructions.
2021-08-28 Removing some warnings.

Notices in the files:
parts and their libraries:
SparkFun-Aesthetics: Licensing: CC v3.0 Share-Alike You are welcome to use this library for commercial purposes.
SparkFun-Resistors: Licensing: Creative Commons ShareAlike 4.0 International - https://creativecommons.org/licenses/by-sa/4.0
SparkFun-Aesthetics: Released under the Creative Commons
